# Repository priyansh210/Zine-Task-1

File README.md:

# Zine-Task-1
Created custom pwm signals using port registers to increase the brightness of an led.

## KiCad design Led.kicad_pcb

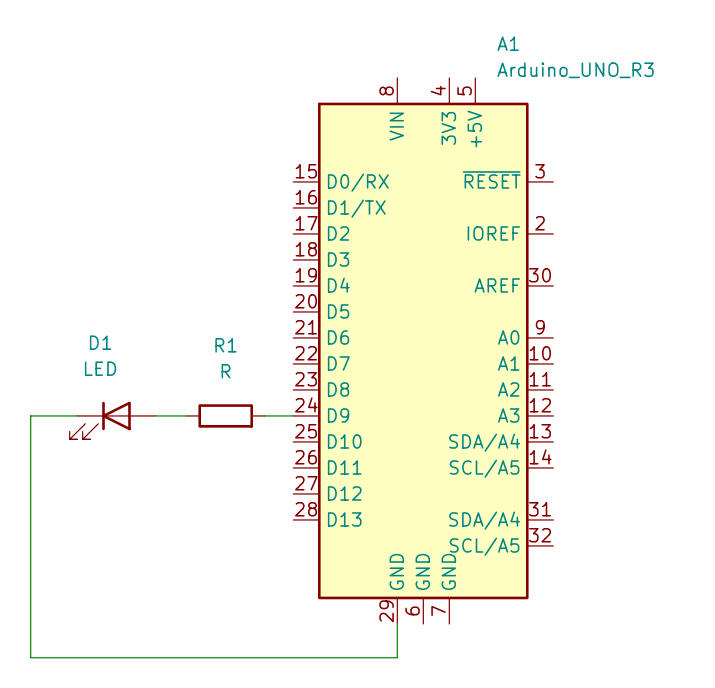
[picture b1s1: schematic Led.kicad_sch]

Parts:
A1: Arduino_UNO_R3
D1: LED
R1: R

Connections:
unnamed: A1.24 (D9), R1.2
unnamed: A1.29 (GND), D1.1 (K)
unnamed: D1.2 (A), R1.1

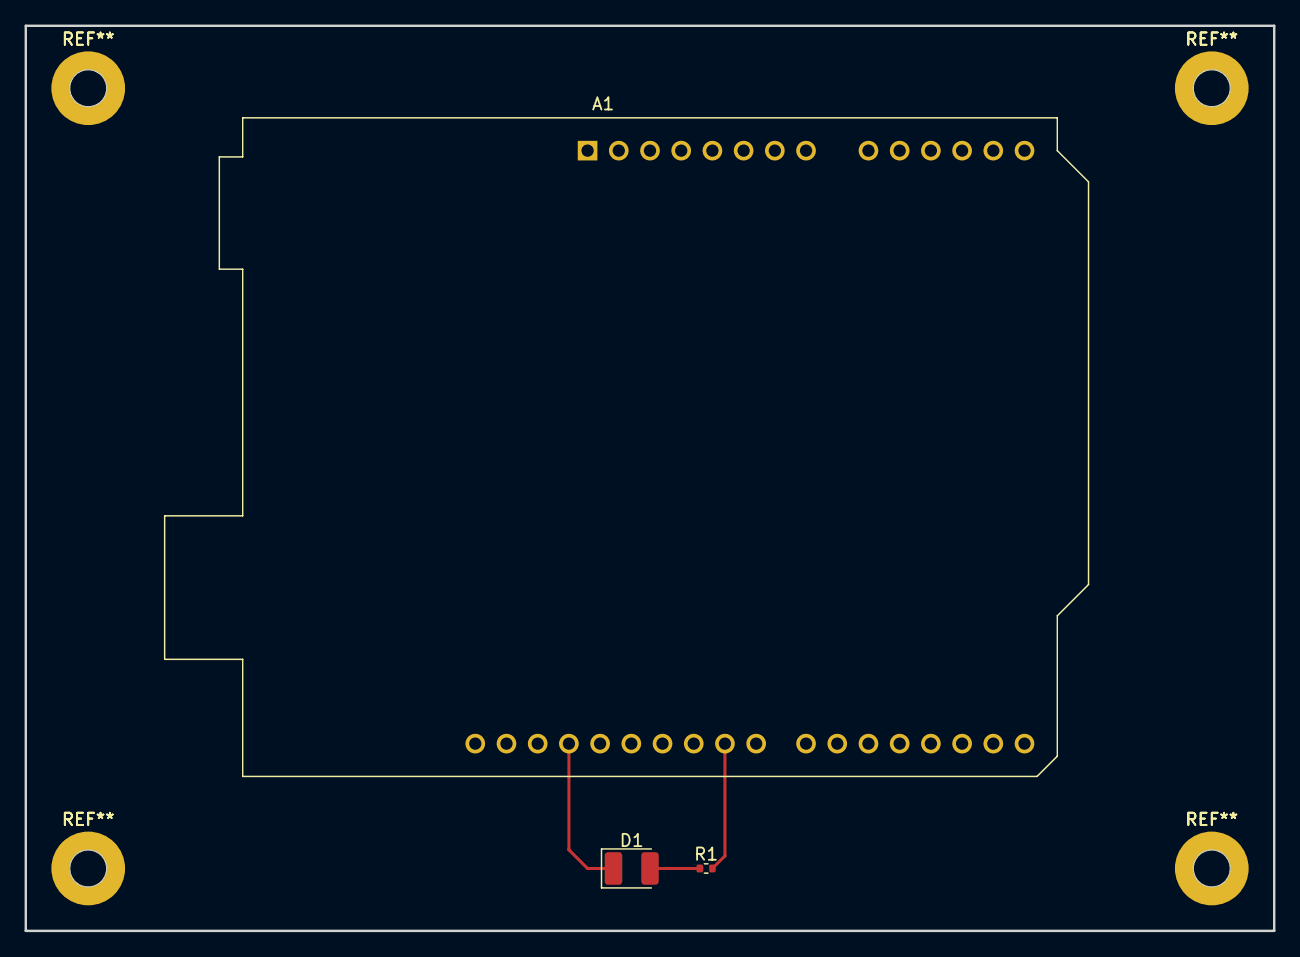
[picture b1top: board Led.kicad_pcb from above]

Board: 2 copper layers, 101.6 x 73.7 mm, 3 parts (0 on the bottom side), 3 nets.

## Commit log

2022-06-12 Updated pcb files
2022-06-12 Project Report
